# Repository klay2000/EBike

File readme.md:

# Ebike

This repo contains the software and CAD files for my ebike.

## Software

All the software is currently written in Arduino and uses a few different libraries.

## Hardware

All the CAD files are made in Fusion 360/KiCAD and are put here in iges format/as a KiCAD project. At the moment my ebike runs a 48 volt 1500w brushless motor running at a maximum of 30 amps. My motor is powered by a FSESC motor controller, which I interface with over UART with a custom ESP32 board. My battery is a 48 volt 13AH li-ion Unit Pack Power battery pack.

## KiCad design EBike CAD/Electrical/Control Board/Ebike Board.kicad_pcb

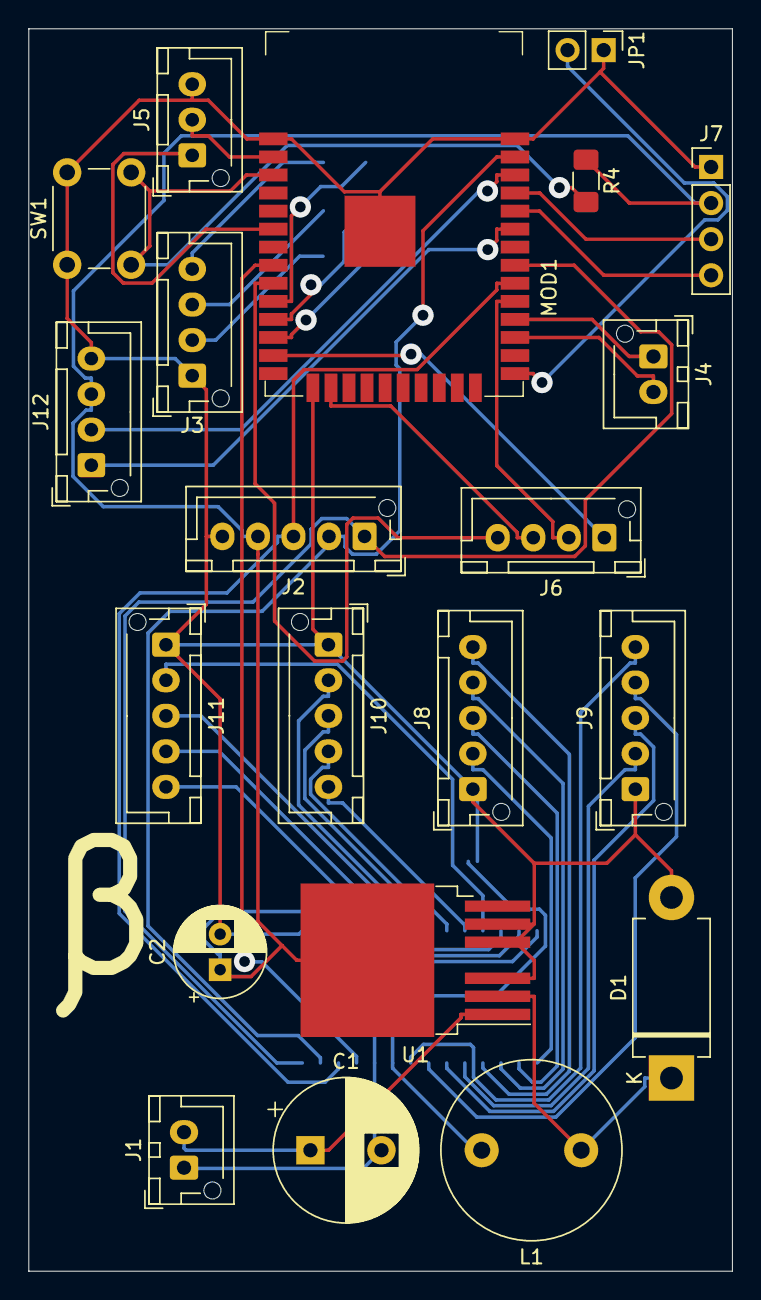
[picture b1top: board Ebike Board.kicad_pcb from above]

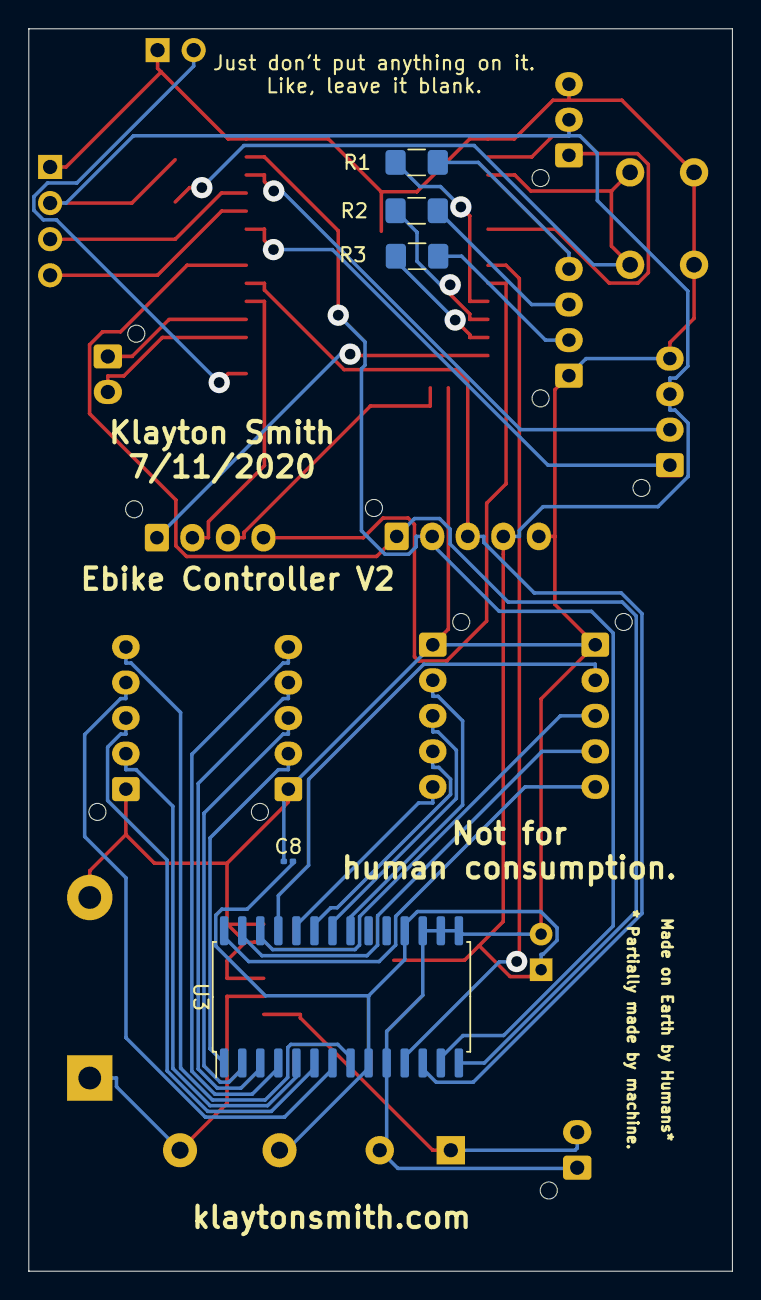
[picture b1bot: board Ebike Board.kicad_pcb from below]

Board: 2 copper layers, 49.5 x 87.4 mm, 26 parts (5 on the bottom side), 43 nets.

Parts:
C1: 100uF; CP_Radial_D10.0mm_P5.00mm
C2: 330uF; CP_Radial_D6.3mm_P2.50mm
C8: 0.1uf; R_0201_0603Metric
D1: SR306; D_DO-201AD_P12.70mm_Horizontal
J1, J4: Conn_01x02_Female; JST_XH_B2B-XH-AM_1x02_P2.50mm_Vertical
J2, J8, J9, J10, J11: Conn_01x05_Female; JST_XH_B5B-XH-AM_1x05_P2.50mm_Vertical
J3, J6, J12: Conn_01x04_Female; JST_XH_B4B-XH-AM_1x04_P2.50mm_Vertical
J5: Conn_01x03_Female; JST_XH_B3B-XH-AM_1x03_P2.50mm_Vertical
J7: 0022232041; PinHeader_1x04_P2.54mm_Vertical
JP1: Jumper_NO_Small; PinHeader_1x02_P2.54mm_Vertical
L1: 330 uH; L_Radial_D12.5mm_P7.00mm_Fastron_09HCP
MOD1: ESP32-WROOM-32; ESP32-WROOM-32D
R1, R2, R3: 65; R_1206_3216Metric_Pad1.42x1.75mm_HandSolder
R4: 10k; R_1206_3216Metric_Pad1.42x1.75mm_HandSolder
SW1: SW_Push; SW_PUSH_6mm
U1: TL2575HV-33IKTTR; TO-263-6
U3: MCP23S17_SO; SOIC-28W_7.5x17.9mm_P1.27mm

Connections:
3v3: C2.1, C8.2, J2.4, J5.2, J7.2, J12.3, L1.2, MOD1.2, R4.1, U1.4, U3.9, U3.18
/ESP32/BOOT: JP1.2, MOD1.25
/ESP32/ExtraCS1: J6.2, MOD1.29
/ESP32/ExtraCS2: J6.3, MOD1.16
/ESP32/ExtraCS3: J6.4, MOD1.9
/ESP32/NFC_CS: J6.1, MOD1.13
/ESP32/RXD: J7.4, MOD1.34
/ESP32/TXD: J7.3, MOD1.35
/ESP32/Throttle: J5.1, MOD1.6
/ESP32/UART_RX: J4.2, MOD1.27
/ESP32/UART_TX: J4.1, MOD1.28
/Power/VBat: C1.1, J1.2, U1.1
GND: C1.2, C2.2, C8.1, D1.2, J1.1, J2.5, J3.1, J5.3, J7.1, J8.1, J9.1, J10.1, J11.1, J12.4, JP1.1, MOD1.1, MOD1.15, MOD1.38, MOD1.39, SW1.1, U1.3, U1.5, U1.6, U3.10, U3.15, U3.16, U3.17
IOExpanderCS: MOD1.8, U3.11
MISO: J2.1, MOD1.31, U3.14
MOSI: J2.2, MOD1.37, U3.13
unnamed: D1.1, L1.1, U1.2
unnamed: J3.2, R3.2
unnamed: J3.3, R2.2
unnamed: J3.4, R1.2
unnamed: J8.2, U3.1
unnamed: J8.3, U3.2
unnamed: J8.4, U3.3
unnamed: J8.5, U3.4
unnamed: J9.2, U3.5
unnamed: J9.3, U3.6
unnamed: J9.4, U3.7
unnamed: J9.5, U3.8
unnamed: J10.2, U3.21
unnamed: J10.3, U3.22
unnamed: J10.4, U3.23
unnamed: J10.5, U3.24
unnamed: J11.2, U3.25
unnamed: J11.3, U3.26
unnamed: J11.4, U3.27
unnamed: J11.5, U3.28
unnamed: MOD1.3, R4.2, SW1.2
unnamed: MOD1.10, R1.1
unnamed: MOD1.11, R2.1
unnamed: MOD1.12, R3.1
SCK: J2.3, MOD1.30, U3.12
SCL: J12.2, MOD1.36
SDA: J12.1, MOD1.33

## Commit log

2019-10-13 Initial
2019-10-14 working drive
2019-10-14 Added readme.
2019-10-14 Fixed markdown problem.
2019-10-16 Restructured
2019-10-17 Added CAD for Battery Clip. Changed readme to reflect new CAD.
2019-10-18 Removed duplicate folder.
2019-10-19 fixed I think
2019-10-20 Actually fixed CAD
2019-11-20 converted cad to fusion, stored in iges format
2019-11-20 converted cad to fusion, stored in iges format (#13)
2019-11-22 Update readme.md
    Fixed Spelling Error
2019-12-17 added cad
2019-12-17 added cad (#19)
2019-12-23 mount works
2019-12-23 Motormount (#21)
    * v1
    * mount works
2019-12-30 added A LOT of CAD
2019-12-30 added A LOT of CAD (#23)
2020-01-12 headlight
2020-01-12 headlight (#26)
2020-01-27 stuff
2020-01-31 Updated STM-32 case to new version.
2020-01-31 Stm32 case update (#28)
    * Updated STM-32 case to new version.
2020-02-02 stuff sorta runs, working on keycard
2020-02-02 wrappers done
2020-02-13 Added some stuff, bike drives.
2020-02-15 finished noun classes
2020-02-15 test
2020-02-16 auth done
2020-02-17 done for night
2020-03-04 removed duplicate CAD folder
2020-04-12 added controller
2020-04-12 Controller cad (#33)
    * stuff
    * stuff sorta runs, working on keycard
    * wrappers done
    * Added some stuff, bike drives.
    * finished noun classes
    * test
2020-05-05 -Software ported to new ESP32 board -Added OTA updates -Added bluetooth serial debug -Added IOexpander -Added headlight functionality
2020-05-05 fixed cad issue
2020-05-05 Software upgrades (#34)
    -Ported to custom ESP32 board
    -Added OTA updates
    -Added bluetooth serial debug
    -Added IOexpander
    -Added headlight functionality
    -Added keycard
2020-07-11 some hacks to fix broken uart and replace it with ppm
2020-07-19 new hw revision
2020-07-19 routed pcb
